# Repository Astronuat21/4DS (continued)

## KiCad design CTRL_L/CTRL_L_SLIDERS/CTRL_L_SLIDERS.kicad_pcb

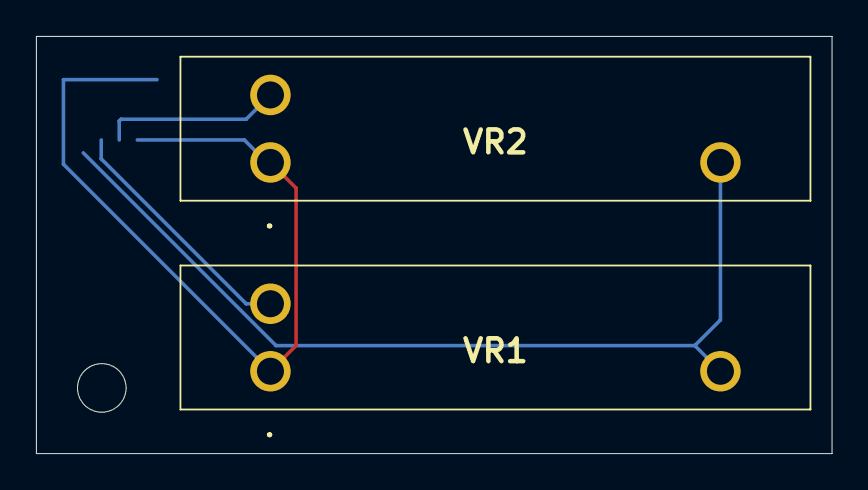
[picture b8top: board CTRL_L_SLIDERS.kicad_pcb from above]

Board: 2 copper layers, 44.2 x 23.2 mm, 3 parts (1 on the bottom side), 4 nets.

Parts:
J1: BM04B-NSHSS-TBT_LF__SN_; BM04BNSHSSTBTLFSN
VR1, VR2: RA2043F-20-10EB1-B10K; RA2043F2010EB1B10K

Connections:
+3V3: J1.4, VR1.3, VR2.3
GND: J1.1, J1.5 (MP1), J1.6 (MP2), VR1.1, VR2.1
SL_BRI: J1.2, VR2.2
SL_VOL: J1.3, VR1.2

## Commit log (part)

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2026-05-08 Second Commit (Test)
2026-05-08 Added README/BAK
2026-05-08 Mini Resistor Update
2026-05-08 Resistor Changes
2026-05-12 New larger layout size (PCB)
2026-05-12 Fixed M.2 Connector Setup
2026-05-12 New Files/README Update
2026-05-12 Routed Wifi; USB_D, TX and RX Dfpairs
2026-05-12 Wifi Card Connected!
2026-05-14 Differential Pairs within 0.003mm variance
2026-05-14 Half Routed USB Tower
2026-05-15 Moved Wifi_LED to GPIO
2026-05-15 Switch to 4-Layer Setup: F.Cu, In.GND, In.PWR, B.Cu
2026-05-20 Split Control Setup, -> L & R
2026-05-22 Joystick Update!
    (Credits to dbenoy for the footprint)
    https://github.com/dbenoy/thumbstick-breakout
2026-05-22 PCB Wiring Complete*
    Updated to JST NSH connector.
    L,XL/Sliders TB moved to another PCB.
2026-05-26 Little bit of Ctrl_R
2026-05-26 Added kinda broken Left Sliders
2026-05-28 sync ASTGW & ASTXPS
2026-05-28 Left Controls Complete* *Omron Switches to be changed
2026-05-28 Removed JYC_4PB, has been superceded by CTRL_L/R
2026-05-29 Wired Ctrl_R! &New AND gate
2026-05-30 CTRL_L updated to use new Diodes.
2026-05-30 Added New Images (\Images)
2026-05-31 Updated CTRL_R to use B3S-1000 Switches
2026-05-31 Updated CTRL_L to use B3S-1000 Switches
2026-05-31 Finished Volume/Brightness Slider Daugherboard!
2026-05-31 Moved JST Connector and added Test Points
2026-05-31 Removed the test points because i dont know what im doing.
2026-06-07 Add LattePandaMu Board files, many fixes to do!
2026-06-07 Added HDMI > LDVS screens
2026-06-08 More work on the Screens
2026-06-10 Mainboard Progress, Updated CTRL-L for new Joystick Module
2026-06-10 Final Cleanup, CTRL-L Likely Complete!
2026-06-11 Updated CTRL-R with New Joystick
2026-06-11 Fixed 3D Model associations on CTRL_L and CTRL_R
2026-06-12 Created CTRL_R_PWR Placeholder files
    Also removed unnecessary "PWR_Button" Global Label in CTRL_R
2026-06-12 Added LICENSE
2026-06-12 README Update
2026-06-13 CTRL_R_PWR Complete!
2026-06-13 Added CTRL_ZL and CTRL_ZR Placeholder files
2026-06-15 added some concept art images
2026-06-19 Added Unpopulated 3D Models of CTRL L&R
2026-06-24 CTRL_Z added, replacement of ZL/ZR
    - The X and ZX shoulder buttons now designed in a vertical only layout akin to joysticks.
    This removes the need for seperate ZL / ZR PCBs. CTRL_Z as a consequence has differing global labels because of the ambiguity.
    This change in design is helpful due to the (5x minimum) nature of ordering PCBs.
2026-06-25 Organized /3D Models
2026-06-27 "Scrapped" the current Mainboard, seems to be very broken for no reason.
    It is being kept for now so that work done for the displays can be copied over later.
2026-06-29 Attempt 3 of the Mainboard. Display-out fully wired
2026-06-29 Renamed "Mainboard" to "Motherboard"
    idk why it wasnt like that before.
